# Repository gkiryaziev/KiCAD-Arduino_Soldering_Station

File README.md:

## KiCAD-Arduino_Soldering_Station

[KiCAD](http://kicad-pcb.org/) [Arduino](https://store.arduino.cc/arduino-nano) Soldering Station

### Info
```
This soldering station was designed for Arduino Nano V3 board.
The code is in the process of development, but if desired, everyone can write their own.
This is an early version of the board and is distributed as is.
The missing 3D models you can find on open resources on the Internet.
```

#### License
```
CC BY 4.0
```

### Screenshot

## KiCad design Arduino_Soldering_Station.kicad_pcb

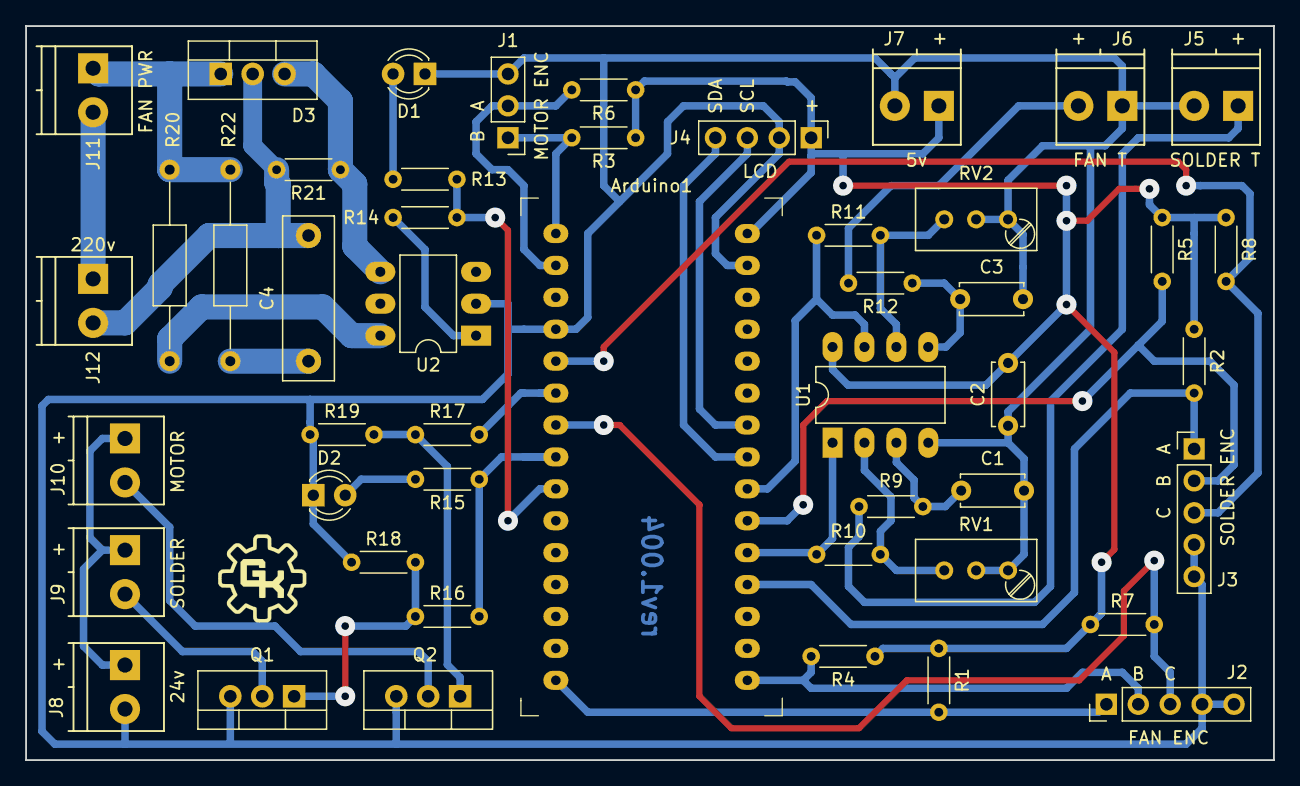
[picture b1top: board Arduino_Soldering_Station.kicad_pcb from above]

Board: 2 copper layers, 99.3 x 58.4 mm, 48 parts (0 on the bottom side), 37 nets.

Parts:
Arduino1: Arduino-Nano-V3; Arduino_Nano
C1, C3: 1uF; C_Disc_D5.0mm_W2.5mm_P5.00mm
C2: 100nF; C_Disc_D5.0mm_W2.5mm_P5.00mm
C4: 10nF; C_Rect_L13.0mm_W4.0mm_P10.00mm_FKS3_FKP3_MKS4
D1: LED FAN; LED_D3.0mm
D2: LED SOLDER; LED_D3.0mm
D3: BT138; TO-220-3_Vertical
J1: Fan Motor Encoder; Pin_Header_Straight_1x03_Pitch2.54mm
J2: Fan Power Encoder; Pin_Header_Straight_1x05_Pitch2.54mm
J3: Solder Power Encoder; Pin_Header_Straight_1x05_Pitch2.54mm
J4: LCD 1602; Pin_Header_Straight_1x04_Pitch2.54mm
J5: Solder Temp; TerminalBlock_Phoenix_PT-3.5mm_2pol
J6: Fan Temp; TerminalBlock_Phoenix_PT-3.5mm_2pol
J7: Power; TerminalBlock_Phoenix_PT-3.5mm_2pol
J8: 24v; TerminalBlock_Phoenix_PT-3.5mm_2pol
J9: Solder Power; TerminalBlock_Phoenix_PT-3.5mm_2pol
J10: Fan Motor; TerminalBlock_Phoenix_PT-3.5mm_2pol
J11: 220V; TerminalBlock_Phoenix_PT-3.5mm_2pol
J12: Fan Power; TerminalBlock_Phoenix_PT-3.5mm_2pol
Q1, Q2: IRFZ44N; TO-220-3_Vertical
R1, R2, R3, R4, R5, R6, R7, R8, R9, R12, R18, R19: 10k; R_Axial_DIN0204_L3.6mm_D1.6mm_P5.08mm_Horizontal
R10, R11: 220k; R_Axial_DIN0204_L3.6mm_D1.6mm_P5.08mm_Horizontal
R13, R14, R15: 220; R_Axial_DIN0204_L3.6mm_D1.6mm_P5.08mm_Horizontal
R16, R17: 100; R_Axial_DIN0204_L3.6mm_D1.6mm_P5.08mm_Horizontal
R20: 380; R_Axial_DIN0207_L6.3mm_D2.5mm_P15.24mm_Horizontal
R21: 330; R_Axial_DIN0204_L3.6mm_D1.6mm_P5.08mm_Horizontal
R22: 39; R_Axial_DIN0207_L6.3mm_D2.5mm_P15.24mm_Horizontal
RV1, RV2: 10k; Potentiometer_Trimmer_Bourns_3296W
U1: LM358; DIP-8_W7.62mm_LongPads
U2: MOC3063M; DIP-6_W7.62mm_LongPads

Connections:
+5V: Arduino1.30, C2.1, J4.1, J7.1, R1.1, R2.1, R3.1, R4.1, R5.1, R6.1, R7.1, R8.1, U1.8
/FAN_ENC_A: Arduino1.15, J2.1, R1.2
/FAN_ENC_B: Arduino1.16, J2.2, R4.2
/FAN_ENC_BTN: Arduino1.7, J2.3, R7.2
/FAN_MOTOR: Arduino1.6, R17.2
/FAN_POWER: Arduino1.9, R13.1, R14.2
/FAN_TEMP: Arduino1.22, R11.1, U1.7
/LCD_SCL: Arduino1.24, J4.3
/LCD_SDA: Arduino1.23, J4.4
/MOTOR_ENC_A: Arduino1.2, J1.2, R6.2
/MOTOR_ENC_B: Arduino1.1, J1.1, R3.2
/SOLDER_ENC_A: Arduino1.19, J3.1, R2.2
/SOLDER_ENC_B: Arduino1.21, J3.2, R5.2
/SOLDER_ENC_BTN: Arduino1.5, J3.3, R8.2
/SOLDER_POWER: Arduino1.8, R15.1, R16.2
/SOLDER_TEMP: Arduino1.20, R10.1, U1.1
GND: Arduino1.4, Arduino1.29, C1.2, C2.2, C3.2, D1.1, D2.1, J1.3, J2.4, J2.5, J3.4, J3.5, J4.2, J5.2, J6.1, J7.2, J8.2, Q1.3, Q2.3, R18.1, R19.1, RV1.1, RV1.2, RV2.1, RV2.2, U1.4, U2.2
unnamed: C1.1, R9.1, U1.3
unnamed: C3.1, R12.1, U1.5
unnamed: C4.1, R22.1
unnamed: C4.2, D3.2, J12.2, R21.2
unnamed: D1.2, R13.2
unnamed: D2.2, R15.2
unnamed: D3.1, J11.1, R20.1, R22.2
unnamed: D3.3, R21.1, U2.4
unnamed: J5.1, R9.2
unnamed: J6.2, R12.2
unnamed: J9.2, Q1.2
unnamed: J8.1, J9.1, J10.1
unnamed: J10.2, Q2.2
unnamed: J11.2, J12.1
unnamed: Q1.1, R16.1, R18.2
unnamed: Q2.1, R17.1, R19.2
unnamed: R10.2, RV1.3, U1.2
unnamed: R11.2, RV2.3, U1.6
unnamed: R14.1, U2.1
unnamed: R20.2, U2.6
